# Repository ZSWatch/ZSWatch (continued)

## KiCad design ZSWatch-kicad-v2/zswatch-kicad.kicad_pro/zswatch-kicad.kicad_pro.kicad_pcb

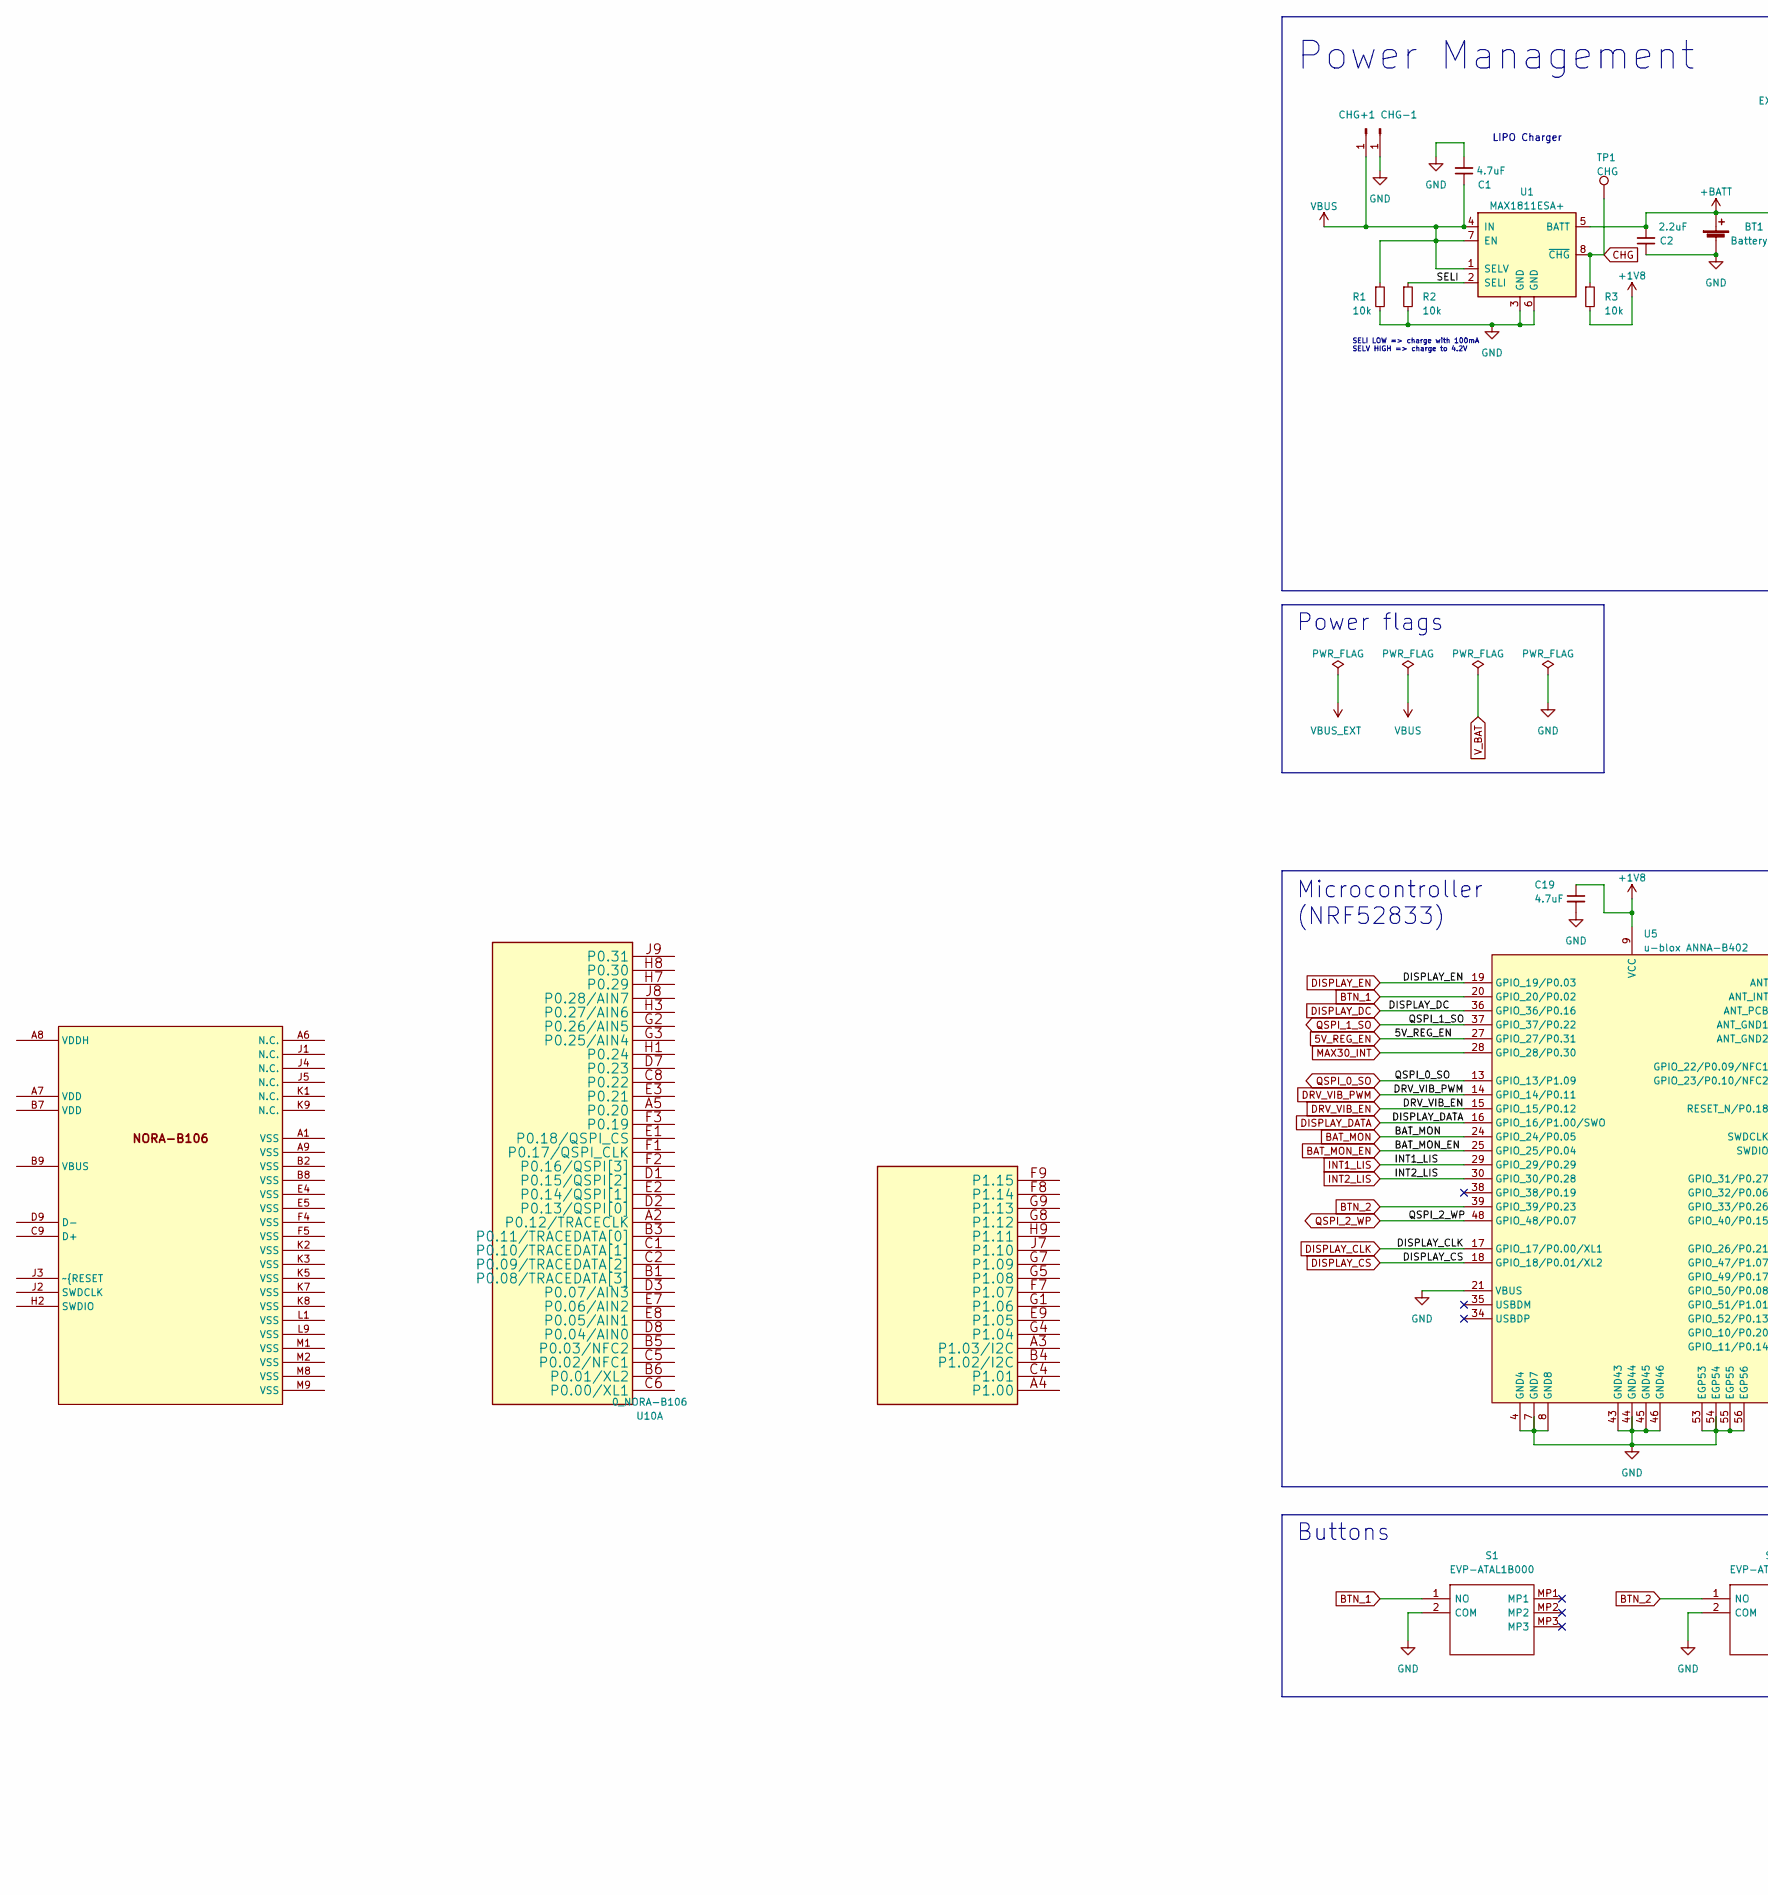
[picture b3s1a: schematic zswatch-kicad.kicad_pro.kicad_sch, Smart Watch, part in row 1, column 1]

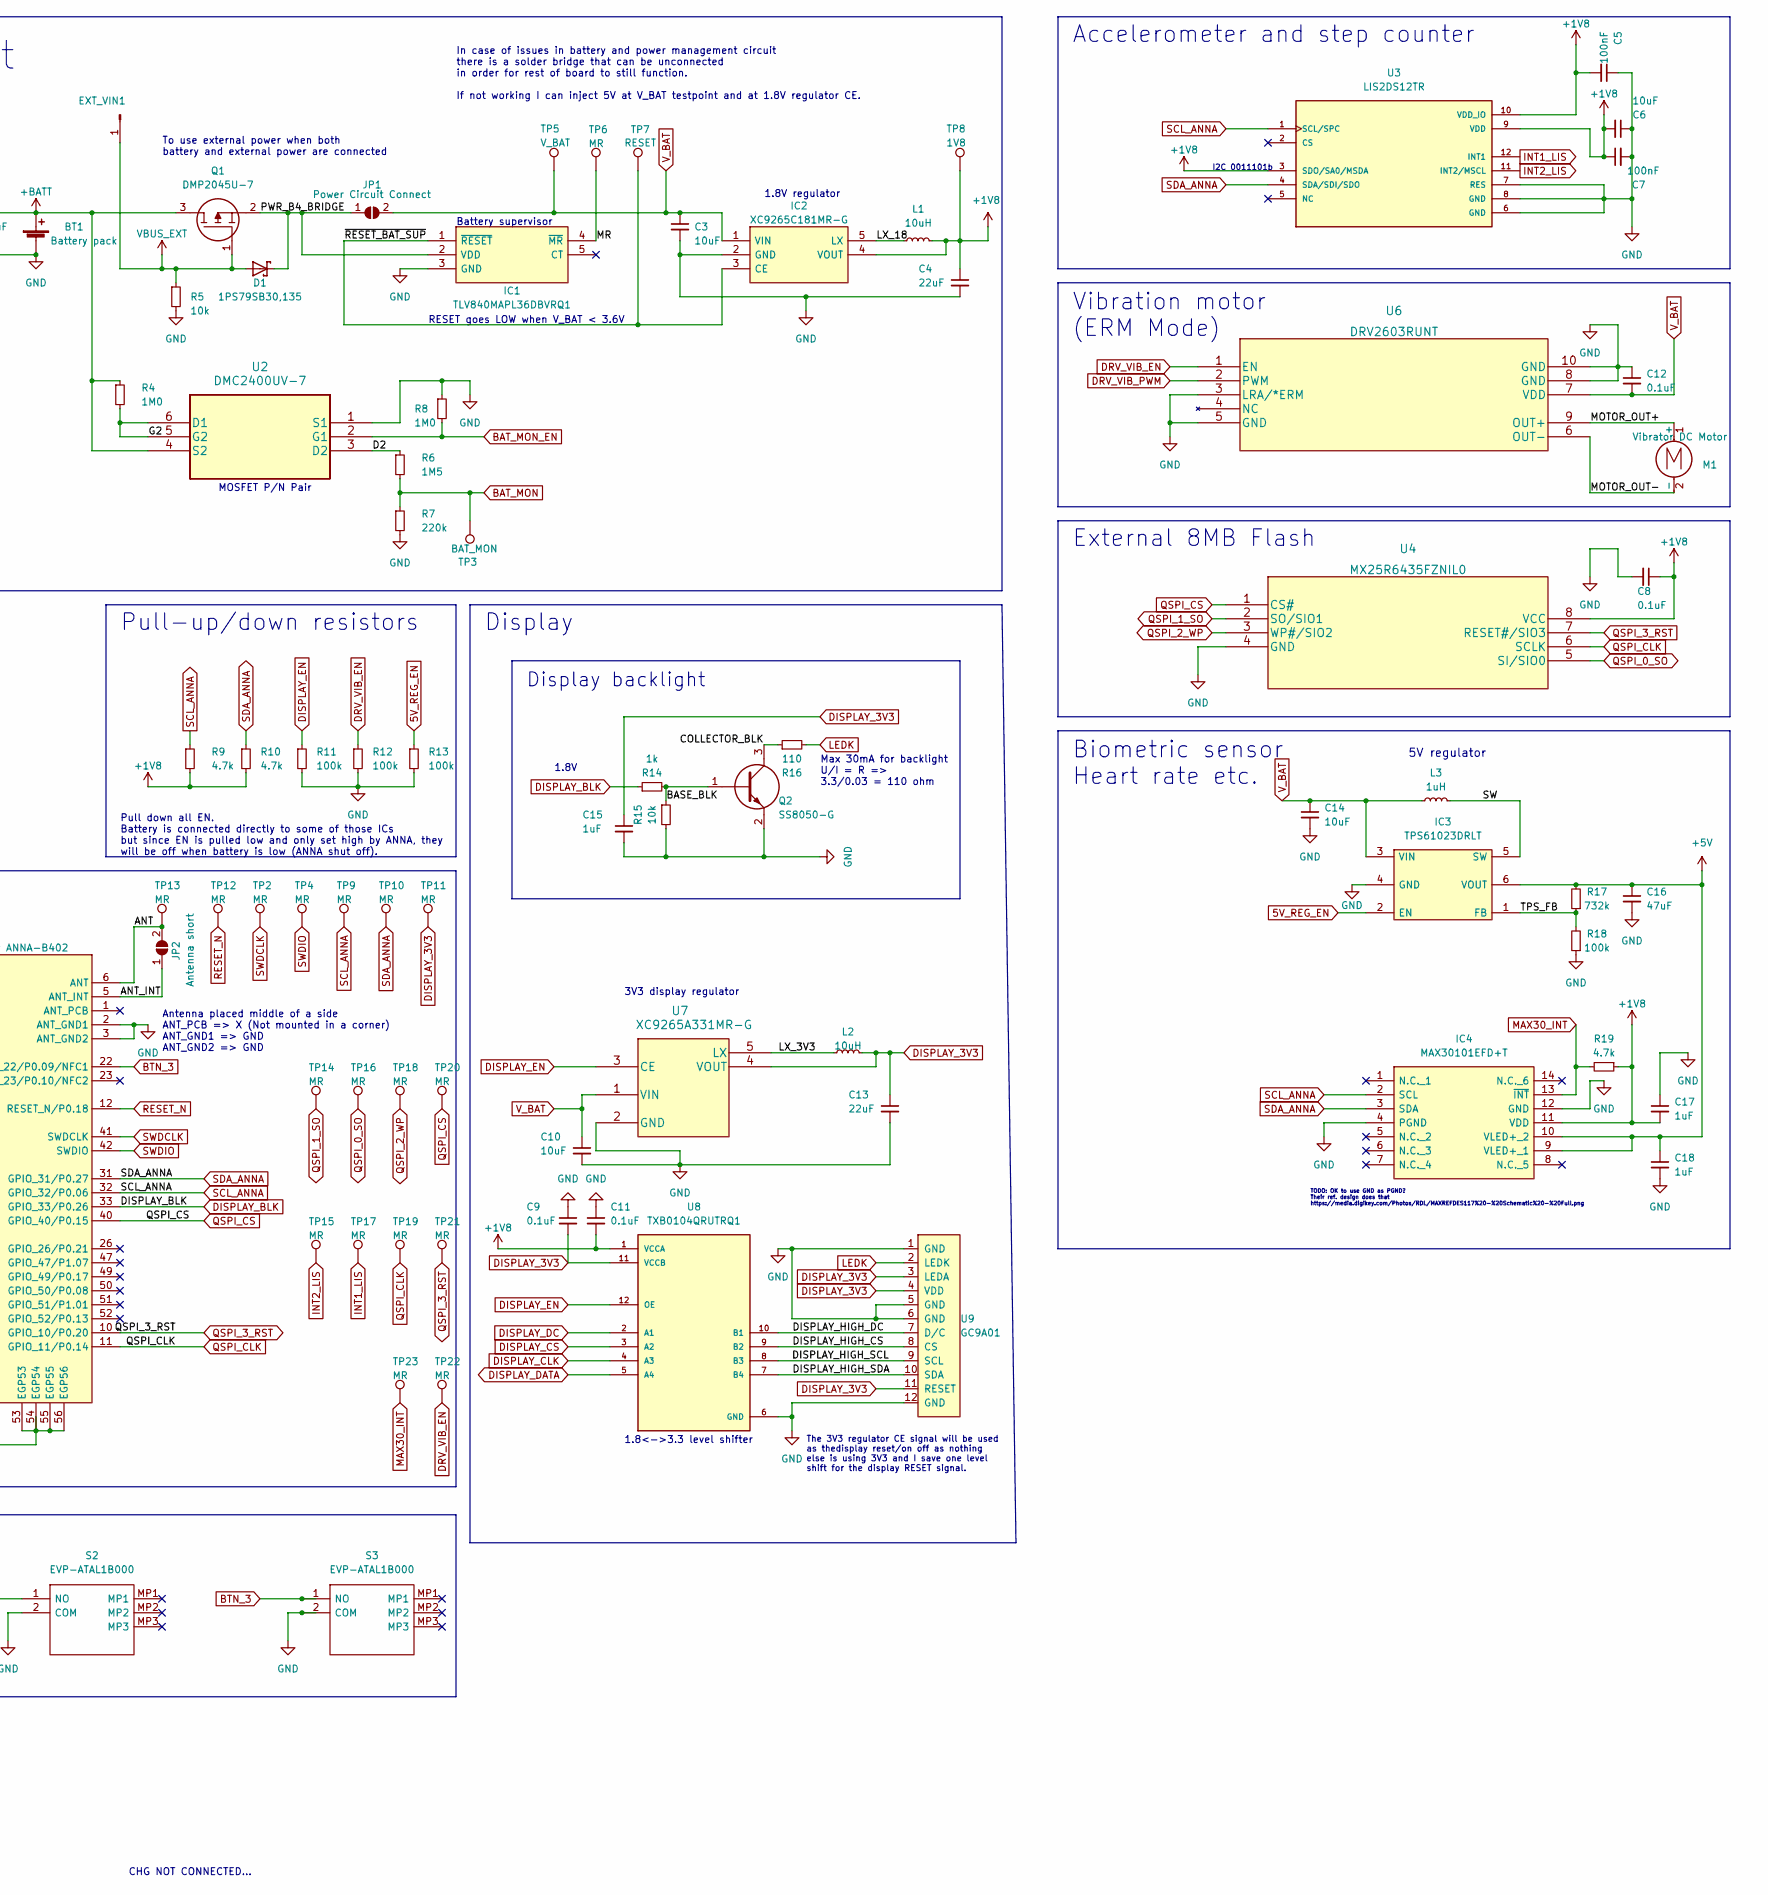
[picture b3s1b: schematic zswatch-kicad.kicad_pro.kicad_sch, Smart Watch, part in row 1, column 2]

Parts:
BT1: Battery pack; SolderWire-0.1sqmm_1x02_P3.6mm_D0.4mm_OD1mm
C1, C19: 4.7uF; C_0603_1608Metric_Pad1.08x0.95mm_HandSolder
C2: 2.2uF; C_0603_1608Metric_Pad1.08x0.95mm_HandSolder
C3, C6, C10, C14: 10uF; C_0603_1608Metric_Pad1.08x0.95mm_HandSolder
C4, C13: 22uF; C_0603_1608Metric_Pad1.08x0.95mm_HandSolder
C5, C7: 100nF; C_0603_1608Metric_Pad1.08x0.95mm_HandSolder
C8, C9, C11, C12: 0.1uF; C_0603_1608Metric_Pad1.08x0.95mm_HandSolder
C15, C17, C18: 1uF; C_0603_1608Metric_Pad1.08x0.95mm_HandSolder
C16: 47uF; C_0603_1608Metric_Pad1.08x0.95mm_HandSolder
CHG+1: Conn_01x01_Male; TestPoint_THTPad_D1.0mm_Drill0.5mm
CHG-1: Conn_01x01_Male; TestPoint_THTPad_D1.0mm_Drill0.5mm
D1: 1PS79SB30,135; SOD523
EXT_VIN1: Conn_01x01_Male; TestPoint_Pad_D1.5mm
IC1: TLV840MAPL36DBVRQ1; SOT95P280X145-5N; Mouser Part Number 595-V840MAPL36DBVRQ1
IC2: XC9265C181MR-G; SOT95P280X130-5N; Mouser Part Number 865-XC9265C181MR-G
IC3: TPS61023DRLT; SOTFL50P160X60-6N; Mouser Part Number 595-TPS61023DRLT
IC4: MAX30101EFD+T; 14-LEAD-OESIP; Mouser Part Number 700-MAX30101EFD+T
JP1: Power Circuit Connect; SolderJumper-2_P1.3mm_Open_RoundedPad1.0x1.5mm
JP2: Antenna short; SolderJumper-2_P1.3mm_Open_Pad1.0x1.5mm
L1, L2: 10uH; L_0603_1608Metric_Pad1.05x0.95mm_HandSolder
L3: 1uH; L_0603_1608Metric_Pad1.05x0.95mm_HandSolder
M1: Vibrator DC Motor; TestPoint_2Pads_Pitch2.54mm_Drill0.8mm
Q1: DMP2045U-7; SOT96P240X110-3N; Mouser Part Number 621-DMP2045U-7
Q2: SS8050-G; SOT95P240X115-3N; Mouser Part Number 750-SS8050-G
R1, R2, R3, R5, R15: 10k; R_0603_1608Metric_Pad0.98x0.95mm_HandSolder
R4, R8: 1M0; R_0603_1608Metric_Pad0.98x0.95mm_HandSolder
R6: 1M5; R_0603_1608Metric_Pad0.98x0.95mm_HandSolder
R7: 220k; R_0603_1608Metric_Pad0.98x0.95mm_HandSolder
R9, R10, R19: 4.7k; R_0603_1608Metric_Pad0.98x0.95mm_HandSolder
R11, R12, R13, R18: 100k; R_0603_1608Metric_Pad0.98x0.95mm_HandSolder
R14: 1k; R_0603_1608Metric_Pad0.98x0.95mm_HandSolder
R16: 110; R_0603_1608Metric_Pad0.98x0.95mm_HandSolder
R17: 732k; R_0603_1608Metric_Pad0.98x0.95mm_HandSolder
S1, S2, S3: EVP-ATAL1B000; EVPATAL1B000; Mouser Part Number 667-EVP-ATAL1B000
TP1: CHG; TestPoint_Pad_D1.0mm
TP2, TP4, TP12: MR; TestPoint_THTPad_D1.0mm_Drill0.5mm
TP3: BAT_MON; TestPoint_Pad_D1.0mm
TP5: V_BAT; TestPoint_Pad_D1.0mm
TP6, TP9, TP10, TP11, TP13: MR; TestPoint_Pad_D1.0mm
TP7: RESET; TestPoint_Pad_D1.0mm
TP8: 1V8; TestPoint_THTPad_D1.0mm_Drill0.5mm
TP14, TP15, TP16, TP17, TP18, TP19, TP20, TP21, TP22, TP23: MR; TestPoint_Pad_D0.4mm
U1: MAX1811ESA+; SOIC127P600X175-8N
U2: DMC2400UV-7
U3: LIS2DS12TR
U4: MX25R6435FZNIL0
U5: u-blox ANNA-B402; ANNA-B402_altium_import
U6: DRV2603RUNT
U7: XC9265A331MR-G; SOT95P280X130-5N
U8: TXB0104QRUTRQ1; HPA01164RUTR; PARTREV 4210580/C 06/12
U9: GC9A01; GC9A01_disp
U10: 0_NORA-B106; NORA_LGA82R_1430X1040X180_ANT; MANUFACTURER P/N NORA-B106-00B

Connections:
5V_REG_EN: IC3.2 (EN), R13.1, U5.27 (GPIO_27/P0.31)
+1V8: C4.1, C5.2, C6.2, C7.1, C8.1, C11.2, C17.2, C19.1, IC2.4 (VOUT), IC4.11 (VDD), L1.2, R3.2, R9.2, R10.2, R19.1, TP8.1, U3.3 (SDO/SA0/MSDA), U3.9 (VDD), U3.10 (VDD_IO), U4.8 (VCC), U5.9 (VCC), U8.1 (VCCA)
+5V: C16.1, C18.1, IC3.6 (VOUT), IC4.9 (VLED+_1), IC4.10 (VLED+_2), R17.2
+BATT: BT1.1 (+), C2.2, Q1.3, R4.1, U1.5 (BATT), U2.4 (S2)
/ANT: JP2.2 (B), TP13.1, U5.6 (ANT)
/ANT_INT: JP2.1 (A), U5.5 (ANT_INT)
/BASE_BLK: Q2.1, R14.2, R15.1
/COLLECTOR_BLK: Q2.3, R16.1
/D2: R6.1, U2.3 (D2)
/DISPLAY_HIGH_CS: U8.9 (B2), U9.8 (CS)
/DISPLAY_HIGH_DC: U8.10 (B1), U9.7 (D/C)
/DISPLAY_HIGH_SCL: U8.8 (B3), U9.9 (SCL)
/DISPLAY_HIGH_SDA: U8.7 (B4), U9.10 (SDA)
/G2: R4.2, U2.5 (G2), U2.6 (D1)
/LX_3V3: L2.1, U7.5 (LX)
/LX_18: IC2.5 (LX), L1.1
/MOTOR_OUT+: M1.1 (+), U6.9 (OUT+)
/MOTOR_OUT-: M1.2 (-), U6.6 (OUT-)
/MR: IC1.4 (~MR), TP6.1
/PWR_B4_BRIDGE: D1.1, IC1.2 (VDD), JP1.1 (A), Q1.2
/SELI: R2.1, U1.2 (SELI)
/SW: IC3.5 (SW), L3.2
/TPS_FB: IC3.1 (FB), R17.1, R18.2
/~RESET_BAT_SUP: IC1.1 (~RESET), IC2.3 (CE), TP7.1
BAT_MON: R6.2, R7.1, TP3.1, U5.24 (GPIO_24/P0.05)
BAT_MON_EN: R8.2, U2.2 (G1), U5.25 (GPIO_25/P0.04)
BTN_1: S1.1 (NO), U5.20 (GPIO_20/P0.02)
BTN_2: S2.1 (NO), U5.39 (GPIO_39/P0.23)
BTN_3: S3.1 (NO), U5.22 (GPIO_22/P0.09/NFC1)
CHG: R3.1, TP1.1, U1.8 (~CHG)
DISPLAY_3V3: C9.2, C13.1, C15.1, L2.2, TP11.1, U7.4 (VOUT), U8.11 (VCCB), U9.3 (LEDA), U9.4 (VDD), U9.11 (RESET)
DISPLAY_BLK: R14.1, U5.33 (GPIO_33/P0.26)
DISPLAY_CLK: U5.17 (GPIO_17/P0.00/XL1), U8.4 (A3)
DISPLAY_CS: U5.18 (GPIO_18/P0.01/XL2), U8.3 (A2)
DISPLAY_DATA: U5.16 (GPIO_16/P1.00/SWO), U8.5 (A4)
DISPLAY_DC: U5.36 (GPIO_36/P0.16), U8.2 (A1)
DISPLAY_EN: R11.1, U5.19 (GPIO_19/P0.03), U7.3 (CE), U8.12 (OE)
DRV_VIB_EN: R12.1, TP22.1, U5.15 (GPIO_15/P0.12), U6.1 (EN)
DRV_VIB_PWM: U5.14 (GPIO_14/P0.11), U6.2 (PWM)
GND: BT1.2 (-), C1.2, C2.1, C3.2, C4.2, C5.1, C6.1, C7.2, C8.2, C9.1, C10.2, C11.1, C12.1, C13.2, C14.2, C15.2, C16.2, C17.1, C18.2, C19.2, CHG-1.1, IC1.3 (GND), IC2.2 (GND), IC3.4 (GND), IC4.4 (PGND), IC4.12 (GND), Q2.2, R1.2, R2.2, R5.2, R7.2, R8.1, R11.2, R12.2, R13.2, R15.2, R18.1, S1.2 (COM), S2.2 (COM), S3.2 (COM), U1.3 (GND), U1.6 (GND), U2.1 (S1), U3.6 (GND), U3.7 (RES), U3.8 (GND), U4.4 (GND), U5.2 (ANT_GND1), U5.3 (ANT_GND2), U5.4 (GND4), U5.7 (GND7), U5.8 (GND8), U5.21 (VBUS), U5.43 (GND43), U5.44 (GND44), U5.45 (GND45), U5.46 (GND46), U5.53 (EGP53), U5.54 (EGP54), U5.55 (EGP55), U5.56 (EGP56), U6.3 (LRA/*ERM), U6.5 (GND), U6.8 (GND), U6.10 (GND), U7.2 (GND), U8.6 (GND), U9.1 (GND), U9.5 (GND), U9.6 (GND), U9.12 (GND)
INT1_LIS: TP17.1, U3.12 (INT1), U5.29 (GPIO_29/P0.29)
INT2_LIS: TP15.1, U3.11 (INT2/MSCL), U5.30 (GPIO_30/P0.28)
LEDK: R16.2, U9.2 (LEDK)
MAX30_INT: IC4.13 (~INT), R19.2, TP23.1, U5.28 (GPIO_28/P0.30)
QSPI_0_SO: TP16.1, U4.5 (SI/SIO0), U5.13 (GPIO_13/P1.09)
QSPI_1_SO: TP14.1, U4.2 (SO/SIO1), U5.37 (GPIO_37/P0.22)
QSPI_2_WP: TP18.1, U4.3 (WP#/SIO2), U5.48 (GPIO_48/P0.07)
QSPI_3_RST: TP21.1, U4.7 (RESET#/SIO3), U5.10 (GPIO_10/P0.20)
QSPI_CLK: TP19.1, U4.6 (SCLK), U5.11 (GPIO_11/P0.14)
QSPI_CS: TP20.1, U4.1 (CS#), U5.40 (GPIO_40/P0.15)
RESET_N: TP12.1, U5.12 (RESET_N/P0.18)
SCL_ANNA: IC4.2 (SCL), R9.1, TP9.1, U3.1 (SCL/SPC), U5.32 (GPIO_32/P0.06)
SDA_ANNA: IC4.3 (SDA), R10.1, TP10.1, U3.4 (SDA/SDI/SDO), U5.31 (GPIO_31/P0.27)
SWDCLK: TP2.1, U5.41 (SWDCLK)
SWDIO: TP4.1, U5.42 (SWDIO)
VBUS: C1.1, CHG+1.1, R1.1, U1.1 (SELV), U1.4 (IN), U1.7 (EN)
VDDA: D1.2, EXT_VIN1.1, Q1.1, R5.1
V_BAT: C3.1, C10.1, C12.2, C14.1, IC2.1 (VIN), IC3.3 (VIN), JP1.2 (B), L3.1, TP5.1, U6.7 (VDD), U7.1 (VIN)

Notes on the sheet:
Display backlight
Biometric sensor Heart rate etc.
Antenna placed middle of a side ANT_PCB => X (Not mounted in a corner) ANT_GND1 => GND ANT_GND2 => GND
Microcontroller (NRF52833)
3V3 display regulator
Pull-up/down resistors
MOSFET P/N Pair
Power Management
SELI LOW => charge with 100mA SELV HIGH => charge to 4.2V
Battery supervisor
RESET goes LOW when V_BAT < 3.6V
CHG NOT CONNECTED...
Buttons
TODO: OK to use GND as PGND? Their ref. design does that https://media.digikey.com/Photos/RDL/MAXREFDES117%20-%20Schematic%20-%20Full.png
Max 30mA for backlight U/I = R => 3.3/0.03 = 110 ohm
In case of issues in battery and power management circuit there is a solder bridge that can be unconnected in order for rest of board to still function. If not working I can inject 5V at V_BAT testpoint and at 1.8V regulator CE.
Power flags
To use external power when both battery and external power are connected
External 8MB Flash
Pull down all EN. Battery is connected directly to some of those ICs but since EN is pulled low and only set high by ANNA, they will be off when battery is low (ANNA shut off).
Accelerometer and step counter
LIPO Charger
_{I2C 0011101b}
5V regulator
1.8<->3.3 level shifter
The 3V3 regulator CE signal will be used as thedisplay reset/on off as nothing else is using 3V3 and I save one level shift for the display RESET signal.
Vibration motor (ERM Mode)
Display
1.8V regulator
1.8V

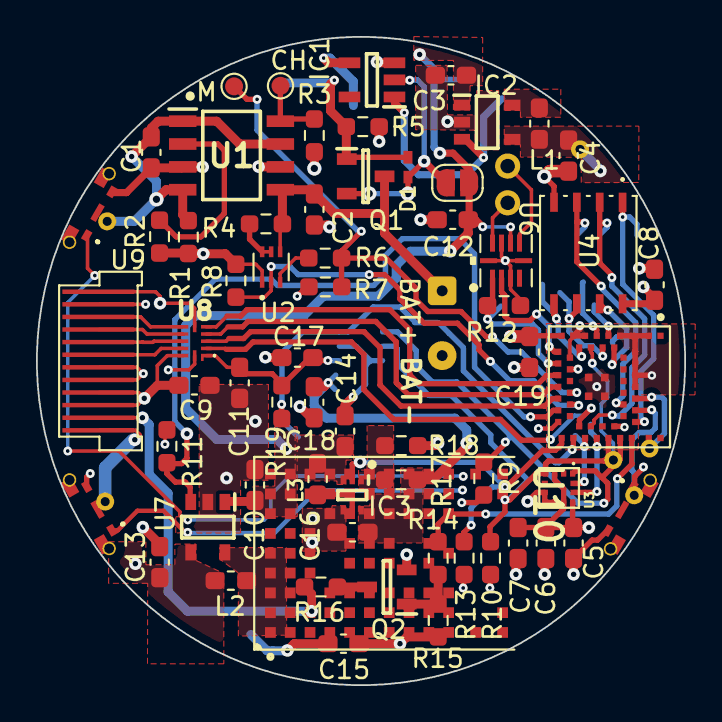
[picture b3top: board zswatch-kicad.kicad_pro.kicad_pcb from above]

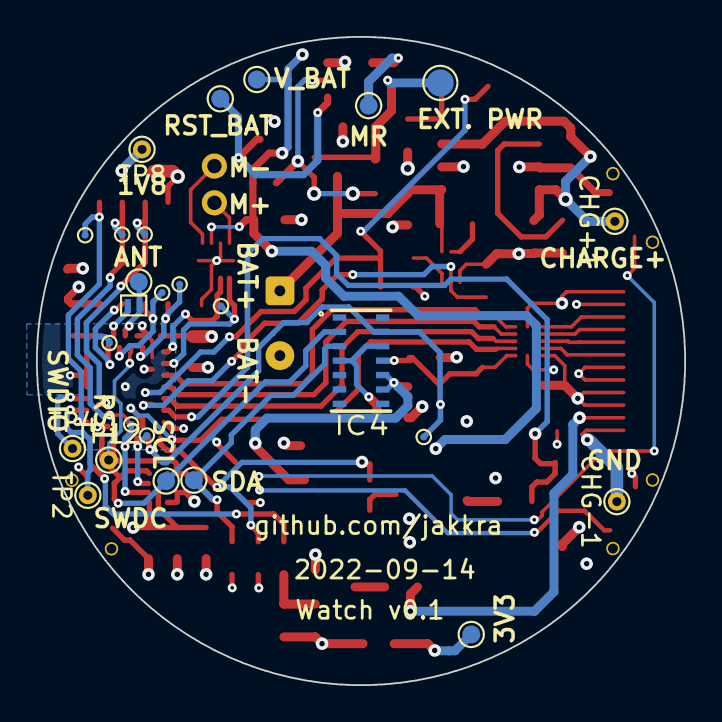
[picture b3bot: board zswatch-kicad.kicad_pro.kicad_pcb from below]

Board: 4 copper layers, 36.0 x 36.0 mm, 91 parts (26 on the bottom side), 58 nets.

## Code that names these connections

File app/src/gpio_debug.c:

#include <zephyr/kernel.h>
#include <zephyr/device.h>
#include <zephyr/sys/__assert.h>
#include <assert.h>
#include <zephyr/drivers/gpio.h>
#include <zephyr/logging/log.h>
#include <gpio_debug.h>

LOG_MODULE_REGISTER(gpio_debug, LOG_LEVEL_WRN);
static struct gpio_dt_spec watch_gpios[] = {
    [TOUCH_RST] = { .port = DEVICE_DT_GET_OR_NULL(DT_NODELABEL(gpio0)), .pin = 20 },
    [TOUCH_SDA] = { .port = DEVICE_DT_GET_OR_NULL(DT_NODELABEL(gpio1)), .pin = 2 },
    [TOUCH_SCL] = { .port = DEVICE_DT_GET_OR_NULL(DT_NODELABEL(gpio1)), .pin = 3 },
    [TOUCH_INT] = { .port = DEVICE_DT_GET_OR_NULL(DT_NODELABEL(gpio1)), .pin = 0 },
    //[DISPLAY_EN] = { .port = DEVICE_DT_GET_OR_NULL(DT_NODELABEL(gpio1)), .pin = 1 },
    //[DISPLAY_RST] = { .port = DEVICE_DT_GET_OR_NULL(DT_NODELABEL(gpio0)), .pin = 23 },
    //[BTN_1] = { .port = DEVICE_DT_GET_OR_NULL(DT_NODELABEL(gpio0)), .pin = 2 },
    //[DISPLAY_DC] = { .port = DEVICE_DT_GET_OR_NULL(DT_NODELABEL(gpio0)), .pin = 16 },
    //[QSPI_1_SO] = { .port = DEVICE_DT_GET_OR_NULL(DT_NODELABEL(gpio0)), .pin = 22 },
    //[V5_REG_EN] = { .port = DEVICE_DT_GET_OR_NULL(DT_NODELABEL(gpio0)), .pin = 31 },
    //[MAX30_INT] = { .port = DEVICE_DT_GET_OR_NULL(DT_NODELABEL(gpio0)), .pin = 30 },
    //[QSPI_0_SO] = { .port = DEVICE_DT_GET_OR_NULL(DT_NODELABEL(gpio1)), .pin = 9 },
    //[DRV_VIB_PWM] = { .port = DEVICE_DT_GET_OR_NULL(DT_NODELABEL(gpio0)), .pin = 11 },
    //[DRV_VIB_EN] = { .port = DEVICE_DT_GET_OR_NULL(DT_NODELABEL(gpio0)), .pin = 12 },
//
    //[DISPLAY_DATA] = { .port = DEVICE_DT_GET_OR_NULL(DT_NODELABEL(gpio1)), .pin = 0 },
    //[BAT_MON] = { .port = DEVICE_DT_GET_OR_NULL(DT_NODELABEL(gpio0)), .pin = 5 },
    //[BAT_MON_EN] = { .port = DEVICE_DT_GET_OR_NULL(DT_NODELABEL(gpio0)), .pin = 4 },
    //[INT1_LIS] = { .port = DEVICE_DT_GET_OR_NULL(DT_NODELABEL(gpio0)), .pin = 29 },
    //[INT2_LIS] = { .port = DEVICE_DT_GET_OR_NULL(DT_NODELABEL(gpio0)), .pin = 28 },
    //[BTN_2] = { .port = DEVICE_DT_GET_OR_NULL(DT_NODELABEL(gpio0)), .pin = 23 },
    //[QSPI_2_WP] = { .port = DEVICE_DT_GET_OR_NULL(DT_NODELABEL(gpio0)), .pin = 7 },
    //[DISPLAY_CLK] = { .port = DEVICE_DT_GET_OR_NULL(DT_NODELABEL(gpio0)), .pin = 0 },
    //[DISPLAY_CS] = { .port = DEVICE_DT_GET_OR_NULL(DT_NODELABEL(gpio0)), .pin = 1 },
//
    //[BTN_3] = { .port = DEVICE_DT_GET_OR_NULL(DT_NODELABEL(gpio0)), .pin = 9},
    //[SDA_ANNA] = { .port = DEVICE_DT_GET_OR_NULL(DT_NODELABEL(gpio0)), .pin = 27 },
    //[SCL_ANNA] = { .port = DEVICE_DT_GET_OR_NULL(DT_NODELABEL(gpio0)), .pin = 6 },
    //[DISPLAY_BLK] = { .port = DEVICE_DT_GET_OR_NULL(DT_NODELABEL(gpio0)), .pin = 26 },
    //[QSPI_CS] = { .port = DEVICE_DT_GET_OR_NULL(DT_NODELABEL(gpio0)), .pin = 15 },
    //[QSPI_3_RST] = { .port = DEVICE_DT_GET_OR_NULL(DT_NODELABEL(gpio0)), .pin = 20 },
    //[QSPI_CLK] = { .port = DEVICE_DT_GET_OR_NULL(DT_NODELABEL(gpio0)), .pin = 14 },
};

static uint8_t pinDefaultState[ARRAY_SIZE(watch_gpios)];



void gpio_debug_init(void)
{
    int ret;
    for (int i = 0; i < ARRAY_SIZE(watch_gpios); i++) {
        __ASSERT(device_is_ready(watch_gpios[i].port), "Error: button device %s is not ready\n",  watch_gpios[i].port->name);
        ret = gpio_pin_configure_dt(&watch_gpios[i], GPIO_OUTPUT);
        __ASSERT_NO_MSG(ret == 0);
        ret = gpio_pin_set_dt(&watch_gpios[i], 0);
        __ASSERT_NO_MSG(ret == 0);
    }
}

static bool check_all_match(gpioWatchId_t skip)
{
    int val;
    bool ret = true;

    for (int i = 0; i < ARRAY_SIZE(watch_gpios); i++) {
        if (i == (int)skip) {
            continue;
        }
        val = gpio_pin_get_dt(&watch_gpios[i]);
        if (val != pinDefaultState[i]) {
            LOG_ERR("Missmatch, pin %d changed value of %d, was %d, expected %d", skip, i, val, pinDefaultState[i]);
            ret = false;
        }
    }
    return ret;
}

void gpio_debug_test_all(void)
{
    int ret;
    bool pass = true;

    // Configure all as input
    for (int i = 0; i < ARRAY_SIZE(watch_gpios); i++) {
        __ASSERT(device_is_ready(watch_gpios[i].port), "Error: button device %s is not ready\n",  watch_gpios[i].port->name);
        ret = gpio_pin_configure_dt(&watch_gpios[i], GPIO_OUTPUT);
        __ASSERT_NO_MSG(ret == 0);
        ret = gpio_pin_set_dt(&watch_gpios[i], 0);
        __ASSERT_NO_MSG(ret == 0);
        k_msleep(10);
        ret = gpio_pin_configure_dt(&watch_gpios[i], GPIO_INPUT | GPIO_PULL_DOWN);
        __ASSERT_NO_MSG(ret == 0);
    }
    k_msleep(1000);
    for (int i = 0; i < ARRAY_SIZE(watch_gpios); i++) {
        int val = gpio_pin_get_dt(&watch_gpios[i]);
        printk("%d => %d\n", i, val);
        pinDefaultState[i] = val;
        k_msleep(10);
    }

    for (int i = 0; i < ARRAY_SIZE(watch_gpios); i++) {
        printk("Check: %d\n", i);
        k_msleep(250);
        ret = gpio_pin_configure_dt(&watch_gpios[i], GPIO_OUTPUT);
        __ASSERT_NO_MSG(ret == 0);
        ret = gpio_pin_set_dt(&watch_gpios[i], 1);
        __ASSERT_NO_MSG(ret == 0);
        k_msleep(250);
        ret = check_all_match(i);
        if (!ret) {
            pass = false;
            printk("Short detected for %d", i);
        }
        ret = gpio_pin_set_dt(&watch_gpios[i], 0);
        __ASSERT_NO_MSG(ret == 0);
        ret = gpio_pin_configure_dt(&watch_gpios[i], GPIO_INPUT | GPIO_PULL_DOWN);
        __ASSERT_NO_MSG(ret == 0);
        k_msleep(250);
    }

    if (pass) {
        printk("No shorts detected!");
    } else {
        printk("Shorts detected!");
    }
}

void gpio_debug_test(gpioWatchId_t gpioId, int val)
{
    LOG_INF("Testing %d (%s.%d)", gpioId, watch_gpios[gpioId].port->name, watch_gpios[gpioId].pin);
    int ret = gpio_pin_configure_dt(&watch_gpios[gpioId], GPIO_OUTPUT);
    __ASSERT_NO_MSG(ret == 0);
    
    ret = gpio_pin_set_dt(&watch_gpios[gpioId], val);
    __ASSERT_NO_MSG(ret == 0);
}
